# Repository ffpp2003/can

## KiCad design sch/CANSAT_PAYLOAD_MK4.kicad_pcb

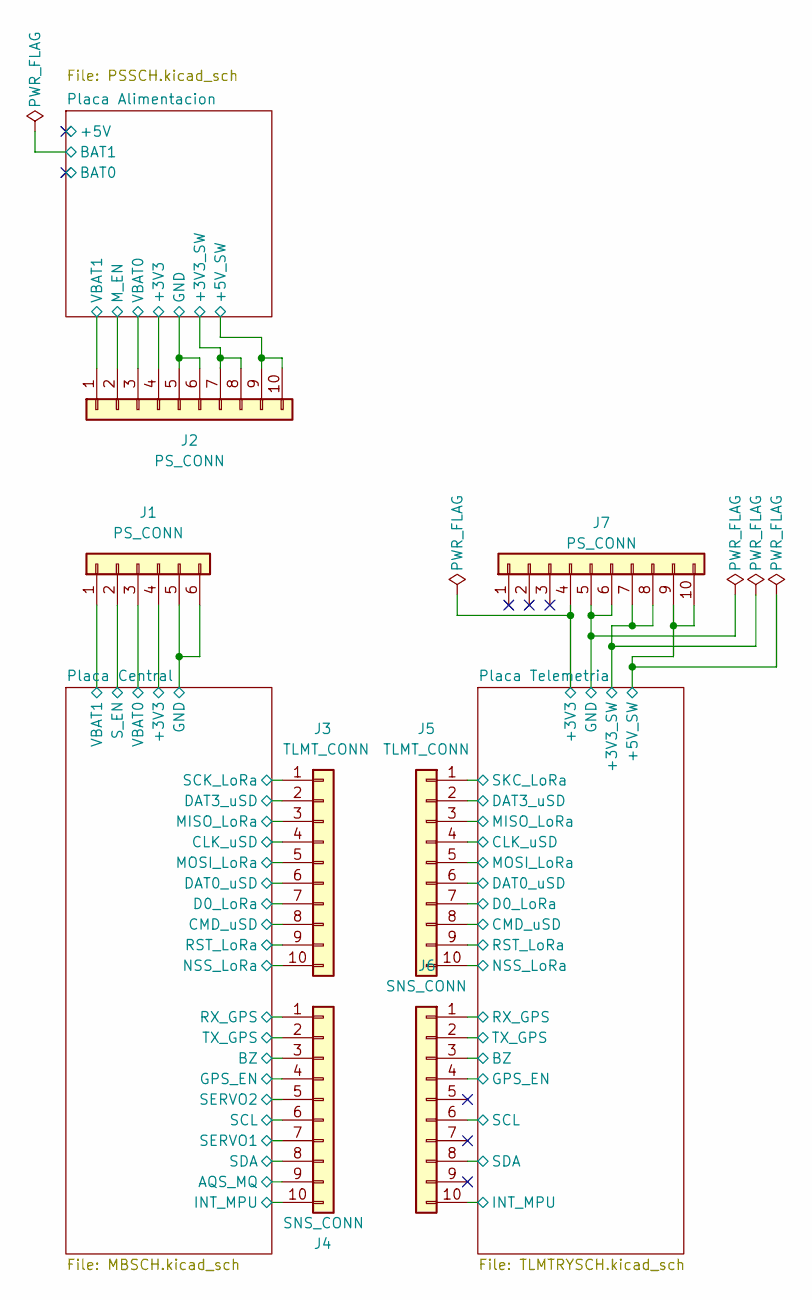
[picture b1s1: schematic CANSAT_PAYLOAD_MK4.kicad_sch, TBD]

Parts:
J1: PS_CONN; PCB_CONN_S
J2, J7: PS_CONN; PCB_CONN
J3, J5: TLMT_CONN; PCB_CONN
J4, J6: SNS_CONN; PCB_CONN

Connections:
/Placa Alimentacion/+3V3: J2.4; also elsewhere on the board
/Placa Alimentacion/+3V3_SW: J2.7, J2.8; also elsewhere on the board
/Placa Alimentacion/+5V_SW: J2.9, J2.10; also elsewhere on the board
/Placa Alimentacion/GND: J2.5, J2.6; also elsewhere on the board
/Placa Alimentacion/M_EN: J2.2; also elsewhere on the board
/Placa Alimentacion/VBAT0: J2.3; also elsewhere on the board
/Placa Alimentacion/VBAT1: J2.1; also elsewhere on the board
/Placa Central/+3V3: J1.4; also elsewhere on the board
/Placa Central/AQS_MQ: J4.9; also elsewhere on the board
/Placa Central/BZ: J4.3; also elsewhere on the board
/Placa Central/CLK_uSD: J3.4; also elsewhere on the board
/Placa Central/CMD_uSD: J3.8; also elsewhere on the board
/Placa Central/D0_LoRa: J3.7; also elsewhere on the board
/Placa Central/DAT0_uSD: J3.6; also elsewhere on the board
/Placa Central/DAT3_uSD: J3.2; also elsewhere on the board
/Placa Central/GND: J1.5, J1.6; also elsewhere on the board
/Placa Central/GPS_EN: J4.4; also elsewhere on the board
/Placa Central/INT_MPU: J4.10; also elsewhere on the board
/Placa Central/MISO_LoRa: J3.3; also elsewhere on the board
/Placa Central/MOSI_LoRa: J3.5; also elsewhere on the board
/Placa Central/NSS_LoRa: J3.10; also elsewhere on the board
/Placa Central/RST_LoRa: J3.9; also elsewhere on the board
/Placa Central/RX_GPS: J4.1; also elsewhere on the board
/Placa Central/SCK_LoRa: J3.1; also elsewhere on the board
/Placa Central/SCL: J4.6; also elsewhere on the board
/Placa Central/SDA: J4.8; also elsewhere on the board
/Placa Central/SERVO1: J4.7; also elsewhere on the board
/Placa Central/SERVO2: J4.5; also elsewhere on the board
/Placa Central/S_EN: J1.2; also elsewhere on the board
/Placa Central/TX_GPS: J4.2; also elsewhere on the board
/Placa Central/VBAT0: J1.3; also elsewhere on the board
/Placa Central/VBAT1: J1.1; also elsewhere on the board
/Placa Telemetria/+3V3: J7.4; also elsewhere on the board
/Placa Telemetria/+3V3_SW: J7.7, J7.8; also elsewhere on the board
/Placa Telemetria/+5V_SW: J7.9, J7.10; also elsewhere on the board
/Placa Telemetria/BZ: J6.3; also elsewhere on the board
/Placa Telemetria/CLK_uSD: J5.4; also elsewhere on the board
/Placa Telemetria/CMD_uSD: J5.8; also elsewhere on the board
/Placa Telemetria/D0_LoRa: J5.7; also elsewhere on the board
/Placa Telemetria/DAT0_uSD: J5.6; also elsewhere on the board
/Placa Telemetria/DAT3_uSD: J5.2; also elsewhere on the board
/Placa Telemetria/GND: J7.5, J7.6; also elsewhere on the board
/Placa Telemetria/GPS_EN: J6.4; also elsewhere on the board
/Placa Telemetria/INT_MPU: J6.10; also elsewhere on the board
/Placa Telemetria/MISO_LoRa: J5.3; also elsewhere on the board
/Placa Telemetria/MOSI_LoRa: J5.5; also elsewhere on the board
/Placa Telemetria/NSS_LoRa: J5.10; also elsewhere on the board
/Placa Telemetria/RST_LoRa: J5.9; also elsewhere on the board
/Placa Telemetria/RX_GPS: J6.1; also elsewhere on the board
/Placa Telemetria/SCL: J6.6; also elsewhere on the board
/Placa Telemetria/SDA: J6.8; also elsewhere on the board
/Placa Telemetria/SKC_LoRa: J5.1; also elsewhere on the board
/Placa Telemetria/TX_GPS: J6.2; also elsewhere on the board

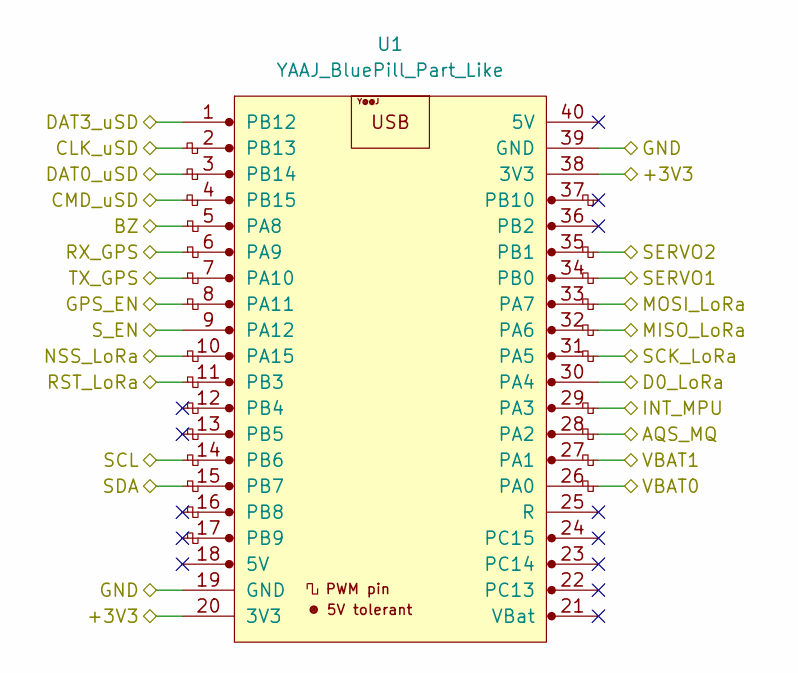
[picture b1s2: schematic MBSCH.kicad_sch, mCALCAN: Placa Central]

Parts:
U1: YAAJ_BluePill_Part_Like; YAAJ_BluePill_2

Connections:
/Placa Central/+3V3: U1.20 (3V3), U1.38 (3V3); also elsewhere on the board
/Placa Central/AQS_MQ: U1.28 (PA2); also elsewhere on the board
/Placa Central/BZ: U1.5 (PA8); also elsewhere on the board
/Placa Central/CLK_uSD: U1.2 (PB13); also elsewhere on the board
/Placa Central/CMD_uSD: U1.4 (PB15); also elsewhere on the board
/Placa Central/D0_LoRa: U1.30 (PA4); also elsewhere on the board
/Placa Central/DAT0_uSD: U1.3 (PB14); also elsewhere on the board
/Placa Central/DAT3_uSD: U1.1 (PB12); also elsewhere on the board
/Placa Central/GND: U1.19 (GND), U1.39 (GND); also elsewhere on the board
/Placa Central/GPS_EN: U1.8 (PA11); also elsewhere on the board
/Placa Central/INT_MPU: U1.29 (PA3); also elsewhere on the board
/Placa Central/MISO_LoRa: U1.32 (PA6); also elsewhere on the board
/Placa Central/MOSI_LoRa: U1.33 (PA7); also elsewhere on the board
/Placa Central/NSS_LoRa: U1.10 (PA15); also elsewhere on the board
/Placa Central/RST_LoRa: U1.11 (PB3); also elsewhere on the board
/Placa Central/RX_GPS: U1.6 (PA9); also elsewhere on the board
/Placa Central/SCK_LoRa: U1.31 (PA5); also elsewhere on the board
/Placa Central/SCL: U1.14 (PB6); also elsewhere on the board
/Placa Central/SDA: U1.15 (PB7); also elsewhere on the board
/Placa Central/SERVO1: U1.34 (PB0); also elsewhere on the board
/Placa Central/SERVO2: U1.35 (PB1); also elsewhere on the board
/Placa Central/S_EN: U1.9 (PA12); also elsewhere on the board
/Placa Central/TX_GPS: U1.7 (PA10); also elsewhere on the board
/Placa Central/VBAT0: U1.26 (PA0); also elsewhere on the board
/Placa Central/VBAT1: U1.27 (PA1); also elsewhere on the board

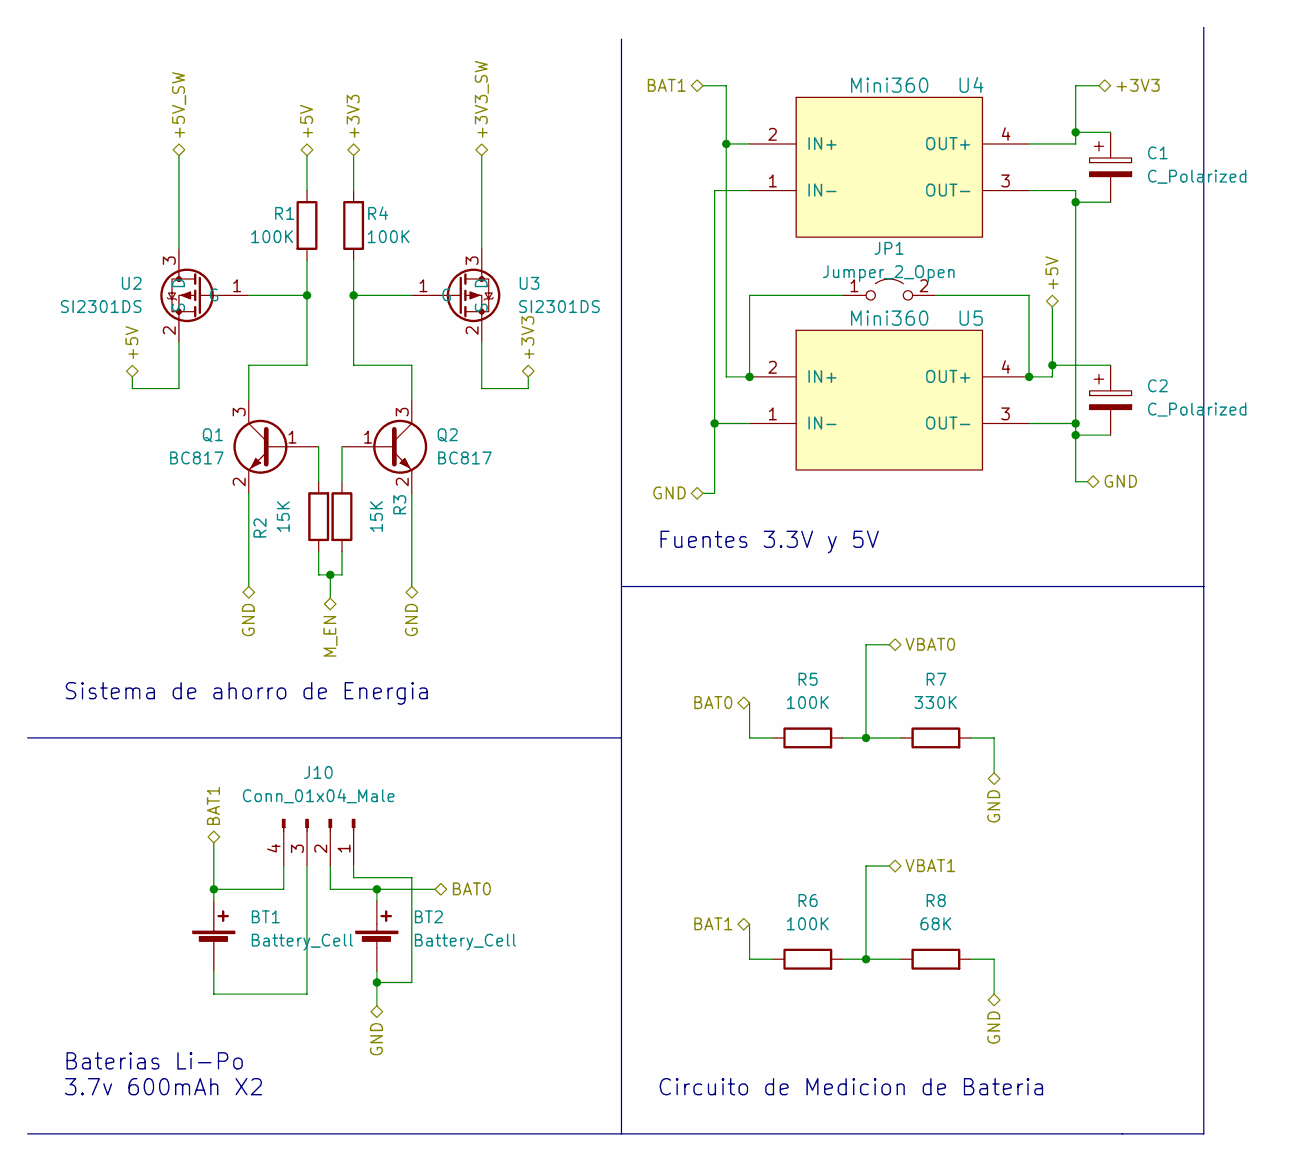
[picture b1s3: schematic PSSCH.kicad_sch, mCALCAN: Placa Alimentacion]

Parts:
BT1, BT2: Battery_Cell; Molex_Micro-Latch_53253-0270_1x02_P2.00mm_Vertical
C1, C2: C_Polarized; CP_EIA-6032-15_Kemet-U_Pad2.25x2.35mm_HandSolder
J10: Conn_01x04_Male; PinHeader_1x04_P2.54mm_Vertical
JP1: Jumper_2_Open; SolderJumper-2_P1.3mm_Open_RoundedPad1.0x1.5mm
Q1, Q2: BC817; SOT-23
R1, R4, R5, R6: 100K; R_0805_2012Metric_Pad1.20x1.40mm_HandSolder
R2, R3: 15K; R_0805_2012Metric_Pad1.20x1.40mm_HandSolder
R7: 330K; R_0805_2012Metric_Pad1.20x1.40mm_HandSolder
R8: 68K; R_0805_2012Metric_Pad1.20x1.40mm_HandSolder
U2, U3: SI2301DS; SOT-23
U4, U5: Mini360; Mini360_step-down

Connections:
/Placa Alimentacion/+3V3: C1.1, R4.2, U3.2 (S), U4.4 (OUT+); also elsewhere on the board
/Placa Alimentacion/+3V3_SW: U3.3 (D); also elsewhere on the board
/Placa Alimentacion/+5V: C2.1, JP1.2 (B), R1.1, U2.2 (S), U5.4 (OUT+)
/Placa Alimentacion/+5V_SW: U2.3 (D); also elsewhere on the board
/Placa Alimentacion/BAT0: BT2.1 (+), J10.2, R5.1
/Placa Alimentacion/BAT1: BT1.1 (+), J10.4, JP1.1 (A), R6.1, U4.2 (IN+), U5.2 (IN+)
/Placa Alimentacion/GND: BT2.2 (-), C1.2, C2.2, J10.1, Q1.2 (E), Q2.2 (E), R7.2, R8.2, U4.1 (IN-), U4.3 (OUT-), U5.1 (IN-), U5.3 (OUT-); also elsewhere on the board
/Placa Alimentacion/M_EN: R2.1, R3.2; also elsewhere on the board
/Placa Alimentacion/VBAT0: R5.2, R7.1; also elsewhere on the board
/Placa Alimentacion/VBAT1: R6.2, R8.1; also elsewhere on the board
unnamed: BT1.2 (-), J10.3
unnamed: Q1.1 (B), R2.2
unnamed: Q1.3 (C), R1.2, U2.1 (G)
unnamed: Q2.1 (B), R3.1
unnamed: Q2.3 (C), R4.1, U3.1 (G)

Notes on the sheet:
Baterias Li-Po 3.7v 600mAh X2
Sistema de ahorro de Energia
Fuentes 3.3V y 5V
Circuito de Medicion de Bateria

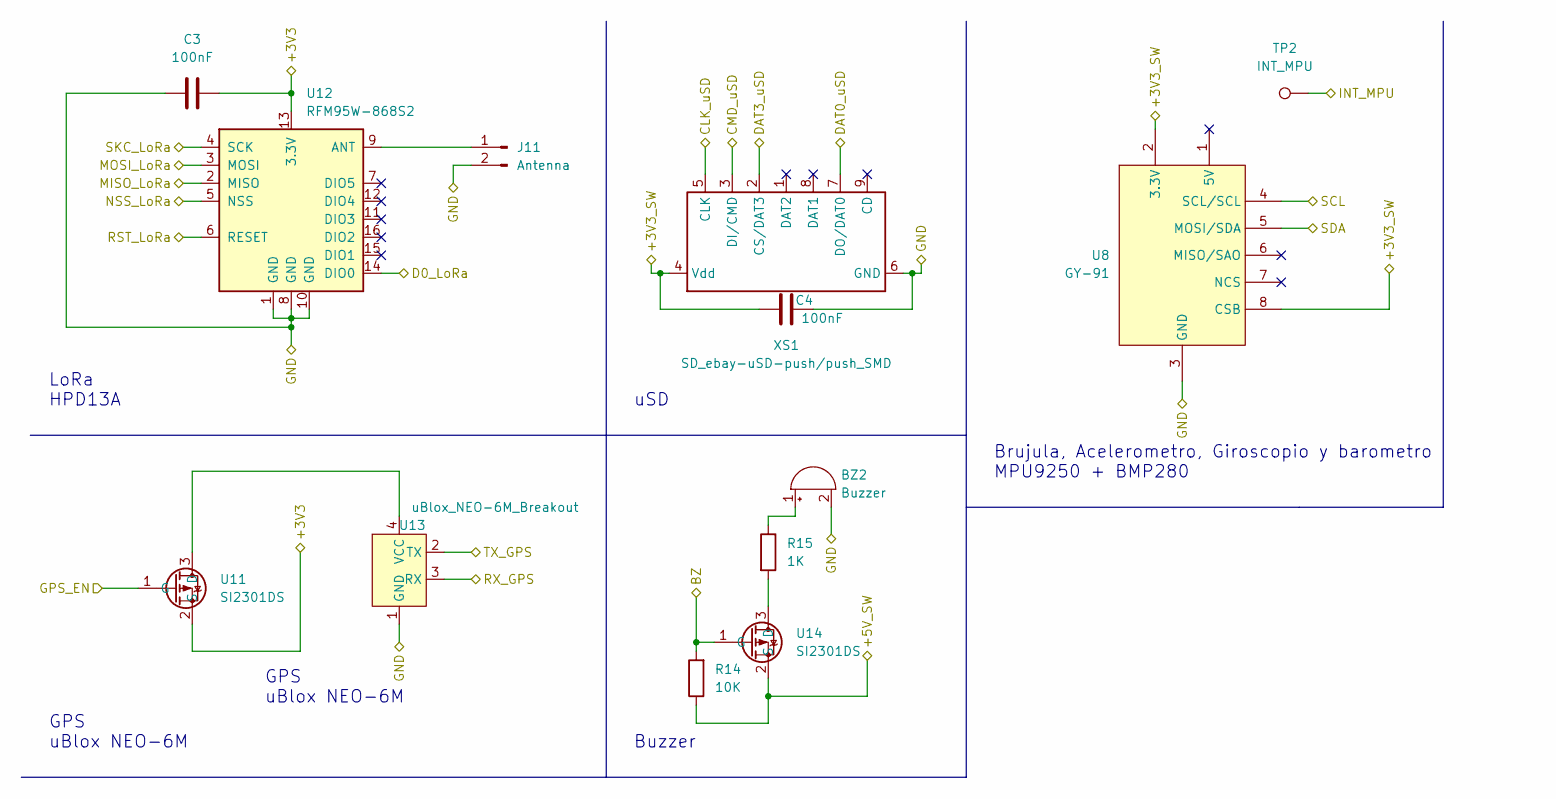
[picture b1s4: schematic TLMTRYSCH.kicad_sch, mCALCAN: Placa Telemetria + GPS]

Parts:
BZ2: Buzzer; Buzzer_12x9.5RM7.6
C3, C4: 100nF; C_0805_2012Metric_Pad1.18x1.45mm_HandSolder
J11: Antenna; U.FL_Molex_MCRF_73412-0110_Vertical
R14: 10K; R_0805_2012Metric_Pad1.20x1.40mm_HandSolder
R15: 1K; R_0805_2012Metric_Pad1.20x1.40mm_HandSolder
TP2: INT_MPU; TestPoint_THTPad_D1.5mm_Drill0.7mm
U8: GY-91; GY-91_Breakout
U11, U14: SI2301DS; SOT-23
U12: RFM95W-868S2; HOPERF_RFM9XW_SMD
U13: uBlox_NEO-6M_Breakout; uBlox-NEO-6M_Breakout
XS1: SD_ebay-uSD-push/push_SMD; Conn_uSDcard

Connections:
/Placa Telemetria/+3V3: C3.2, U11.2 (S), U12.13 (3.3V); also elsewhere on the board
/Placa Telemetria/+3V3_SW: C4.1, U8.2 (3.3V), U8.8 (CSB), XS1.4 (Vdd); also elsewhere on the board
/Placa Telemetria/+5V_SW: R14.1, U14.2 (S); also elsewhere on the board
/Placa Telemetria/BZ: R14.2, U14.1 (G); also elsewhere on the board
/Placa Telemetria/CLK_uSD: XS1.5 (CLK); also elsewhere on the board
/Placa Telemetria/CMD_uSD: XS1.3 (DI/CMD); also elsewhere on the board
/Placa Telemetria/D0_LoRa: U12.14 (DIO0); also elsewhere on the board
/Placa Telemetria/DAT0_uSD: XS1.7 (DO/DAT0); also elsewhere on the board
/Placa Telemetria/DAT3_uSD: XS1.2 (CS/DAT3); also elsewhere on the board
/Placa Telemetria/GND: BZ2.2 (+), C3.1, C4.2, J11.2, U8.3 (GND), U12.1 (GND), U12.8 (GND), U12.10 (GND), U13.1 (GND), XS1.6 (GND); also elsewhere on the board
/Placa Telemetria/GPS_EN: U11.1 (G); also elsewhere on the board
/Placa Telemetria/INT_MPU: TP2.1; also elsewhere on the board
/Placa Telemetria/MISO_LoRa: U12.2 (MISO); also elsewhere on the board
/Placa Telemetria/MOSI_LoRa: U12.3 (MOSI); also elsewhere on the board
/Placa Telemetria/NSS_LoRa: U12.5 (NSS); also elsewhere on the board
/Placa Telemetria/RST_LoRa: U12.6 (RESET); also elsewhere on the board
/Placa Telemetria/RX_GPS: U13.3 (RX); also elsewhere on the board
/Placa Telemetria/SCL: U8.4 (SCL/SCL); also elsewhere on the board
/Placa Telemetria/SDA: U8.5 (MOSI/SDA); also elsewhere on the board
/Placa Telemetria/SKC_LoRa: U12.4 (SCK); also elsewhere on the board
/Placa Telemetria/TX_GPS: U13.2 (TX); also elsewhere on the board
unnamed: BZ2.1 (-), R15.1
unnamed: J11.1, U12.9 (ANT)
unnamed: U11.3 (D), U13.4 (VCC)
unnamed: R15.2, U14.3 (D)

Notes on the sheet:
GPS uBlox NEO-6M
LoRa HPD13A
Brujula, Acelerometro, Giroscopio y barometro MPU9250 + BMP280
uSD
Buzzer

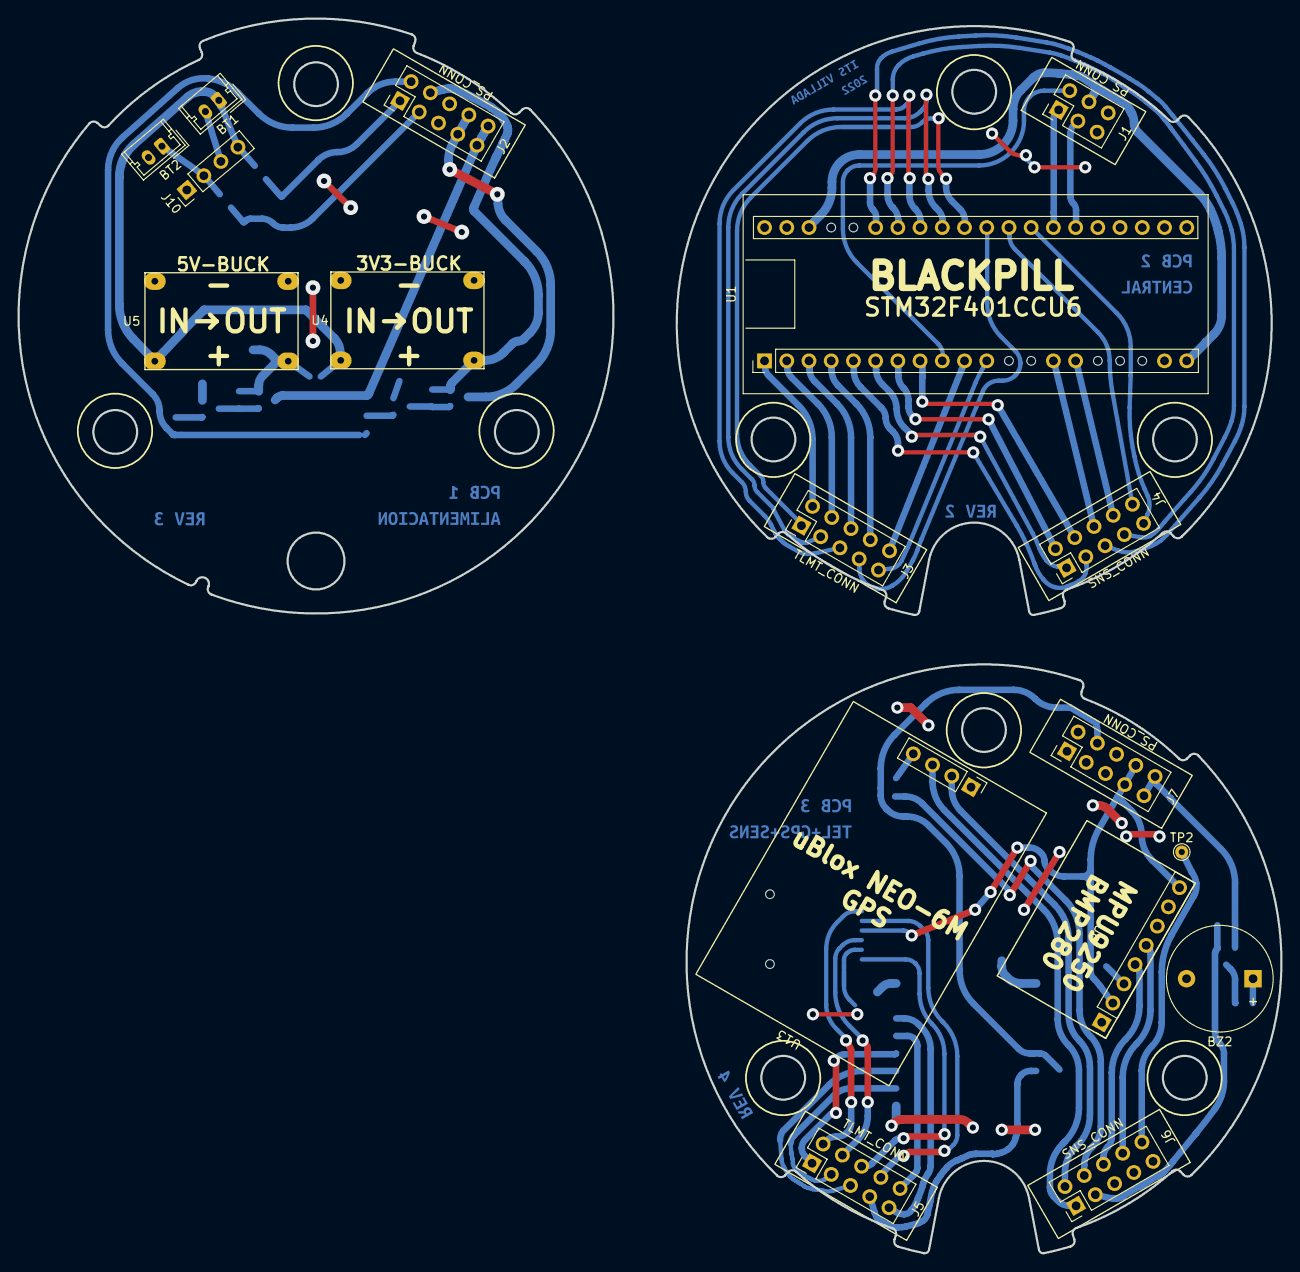
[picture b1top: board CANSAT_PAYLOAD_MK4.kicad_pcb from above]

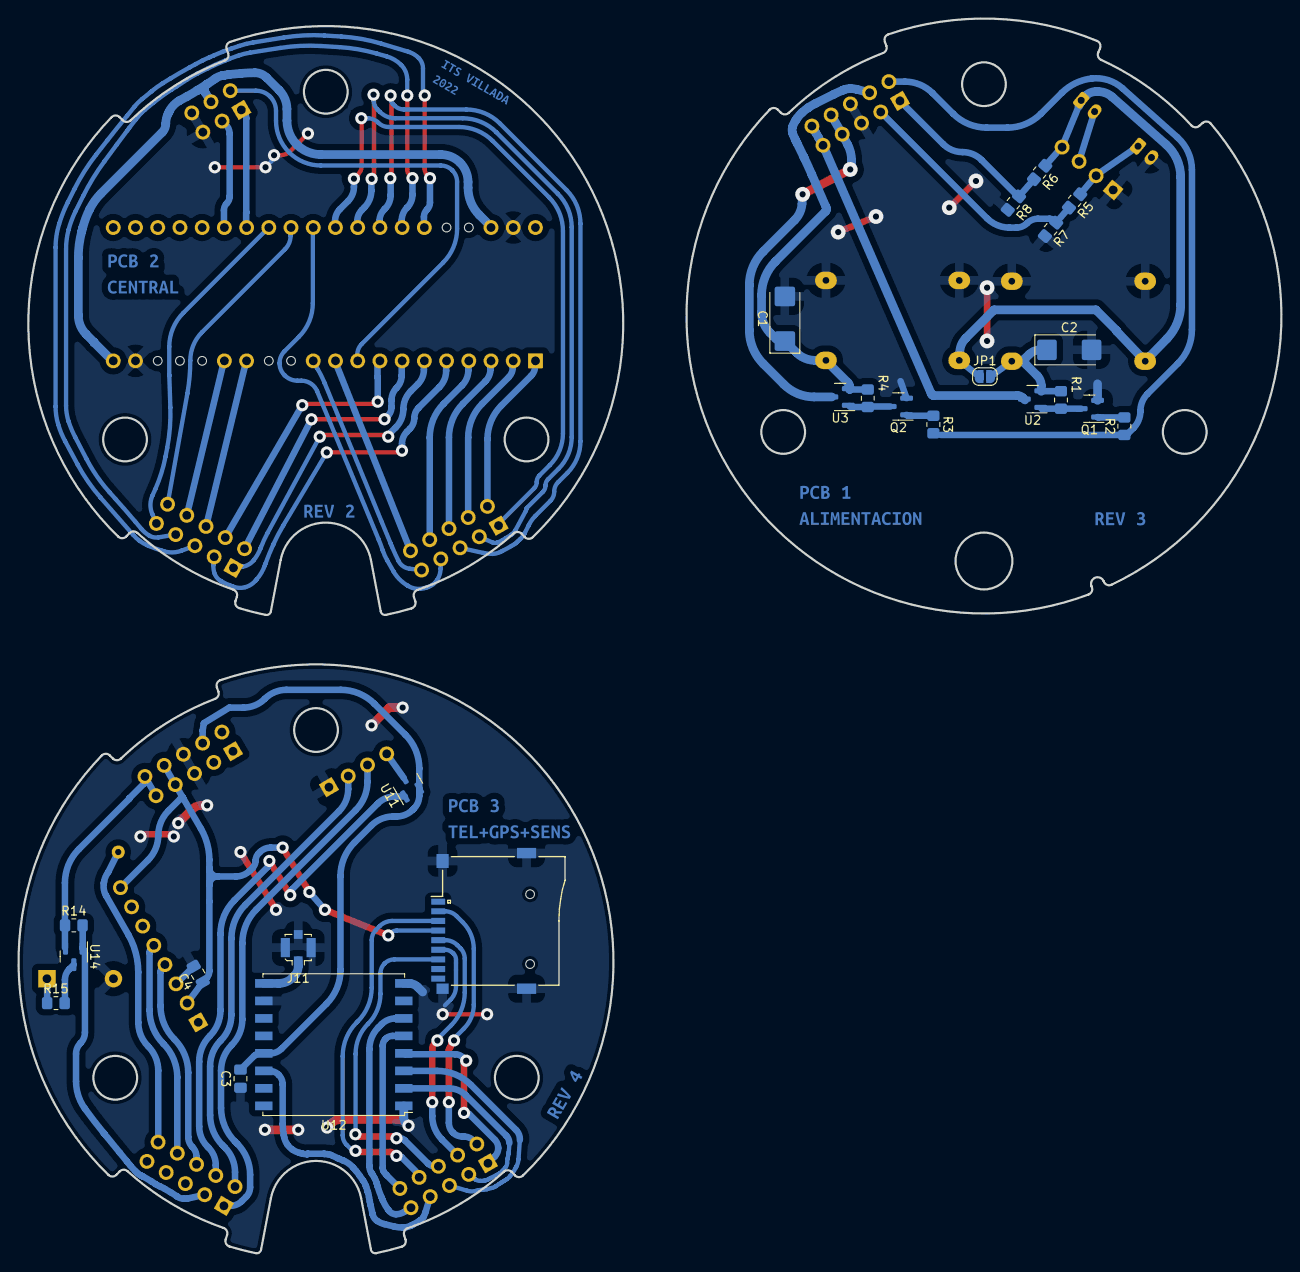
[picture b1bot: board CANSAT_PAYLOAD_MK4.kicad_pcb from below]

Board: 2 copper layers, 144.4 x 141.1 mm, 48 parts (31 on the bottom side), 65 nets.

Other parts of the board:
kibuzzard-655ED218: G***; kibuzzard-655ED218
kibuzzard-655ED392: G***; kibuzzard-655ED392
kibuzzard-655F6654: G***; kibuzzard-655F6654
kibuzzard-6319D247: G***; kibuzzard-6319D247
kibuzzard-63173E9C: G***; kibuzzard-63173E9C
kibuzzard-63173EF4: G***; kibuzzard-63173EF4
kibuzzard-634739B3: G***; kibuzzard-634739B3

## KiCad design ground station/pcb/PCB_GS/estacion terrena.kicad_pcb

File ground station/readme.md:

# Estacion Terrena

La estacion terrena del proyecto cumple la funcion de recibir los datos de la telemetria del cansat y enviarlas a la computadora a traves del puerto serial
tambien tiene la capacidad de cargar las baterias del cansat

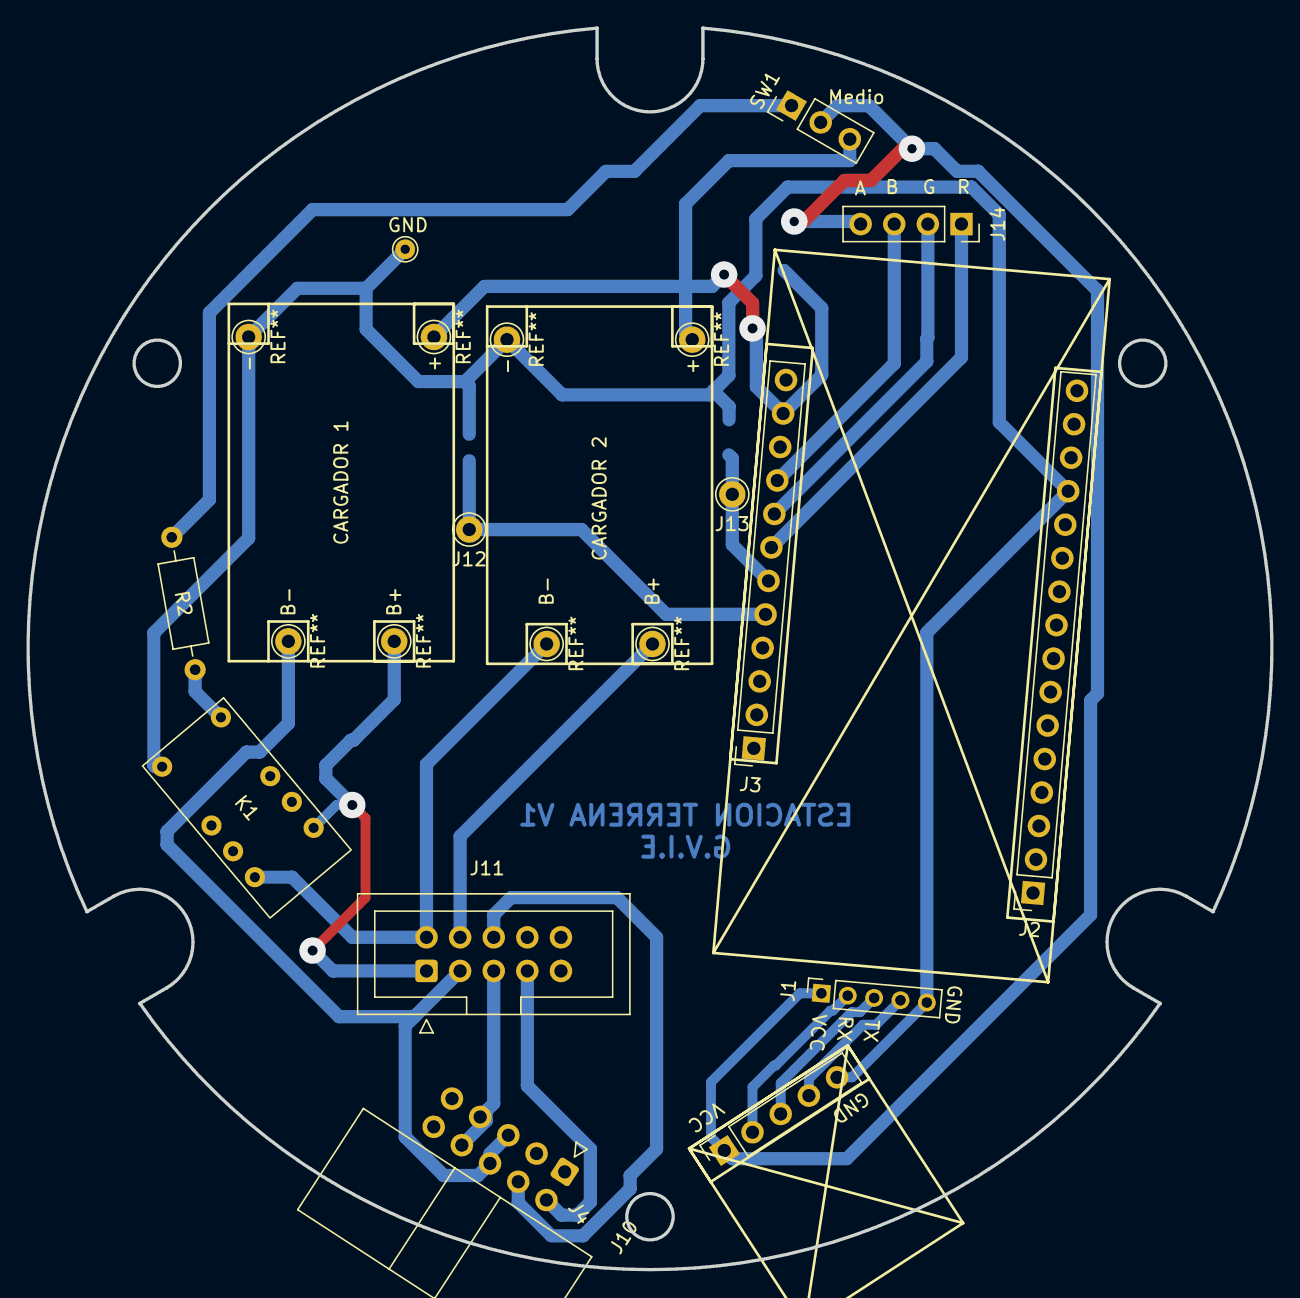
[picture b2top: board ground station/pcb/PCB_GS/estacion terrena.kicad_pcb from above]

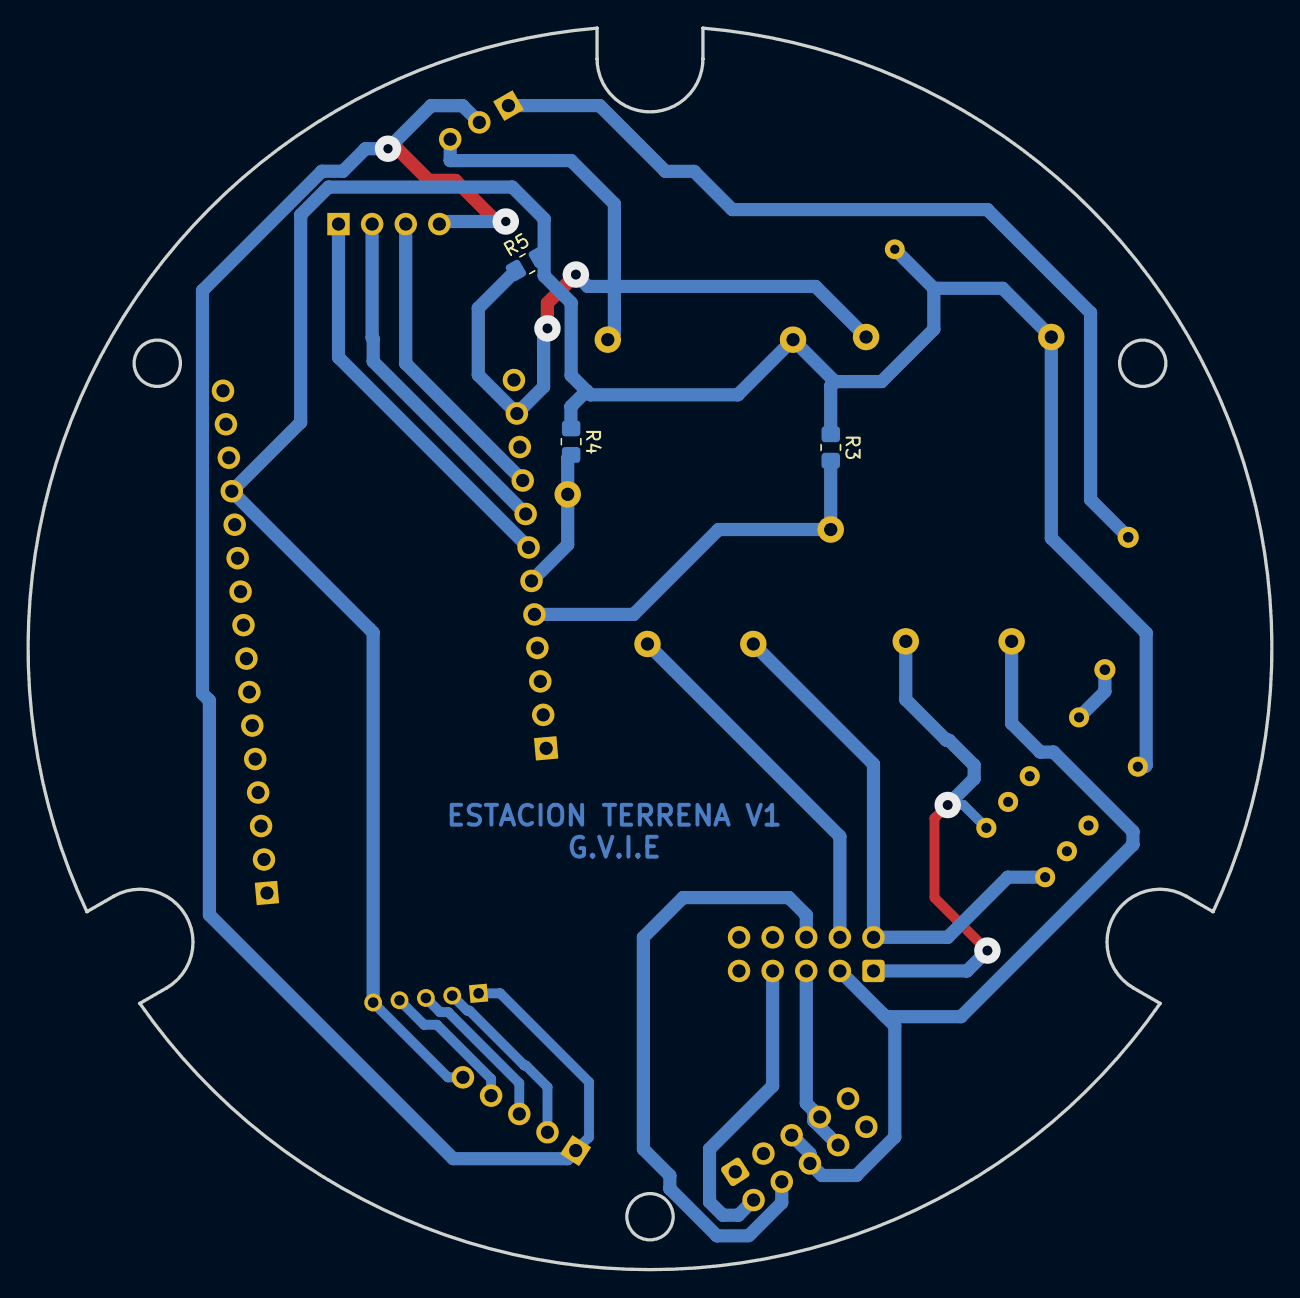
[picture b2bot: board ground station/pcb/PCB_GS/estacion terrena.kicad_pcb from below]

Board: 2 copper layers, 94.0 x 93.8 mm, 16 parts (3 on the bottom side), 19 nets.

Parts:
GND: TestPoint_THTPad_D1.5mm_Drill0.7mm
J1: Micro-usb_lora; PinSocket_1x05_P2.00mm_Vertical
J2: Parte izquierda lora; PinSocket_1x16_P2.54mm_Vertical
J3: parte derecha lora; PinSocket_1x12_P2.54mm_Vertical
J4: Breakouy_micro_usb; PinSocket_1x05_P2.54mm_Vertical
J10: IDC_STLINK; IDC-Header_2x05_P2.54mm_Horizontal
J11: IDC_CANSAT; IDC-Header_2x05_P2.54mm_Vertical
J12: LED_CARGA_1; Pin_D1.0mm_L10.0mm
J13: LED_CARGA_2; Pin_D1.0mm_L10.0mm
J14: conector RGB; PinSocket_1x04_P2.54mm_Vertical
K1: ADW11; RELAY PANASONIC
R2: 120; R_Axial_DIN0207_L6.3mm_D2.5mm_P10.16mm_Horizontal
R3, R4, R5: 10K; R_0805_2012Metric_Pad1.20x1.40mm_HandSolder
SW1: SWITCH; PinHeader_1x03_P2.54mm_Vertical

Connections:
/B: J3.9, J14.3
/G: J3.8, J14.2
/GNDBAT2: J11.2, K1.5
/LED_CARGA_1: J3.5, J12.1, R3.2
/LED_CARGA_2: J3.6, J13.1, R4.2
/NC: J1.4, J4.4
/R: J3.7, J14.1
/RX: J1.2, J4.2
/SCLK _STL_LINK: J10.2, J11.7
/SDIO_STL: J10.4, J11.6
/TX: J1.3, J4.3
/VBAT1: J11.1, K1.3
/VCC_STLINK: J10.7, J10.8, J11.5
/VCC_SW: J3.11, R5.1, SW1.3 (C)
GND: GND.1, J1.5, J2.13, J4.5, K1.6, R3.1, R4.1, R5.2
GND1: J10.5, J10.6, J11.3
unnamed: K1.1, R2.2
unnamed: R2.1, SW1.1 (A)
VCC: J1.1, J4.1, J14.4, SW1.2 (B)

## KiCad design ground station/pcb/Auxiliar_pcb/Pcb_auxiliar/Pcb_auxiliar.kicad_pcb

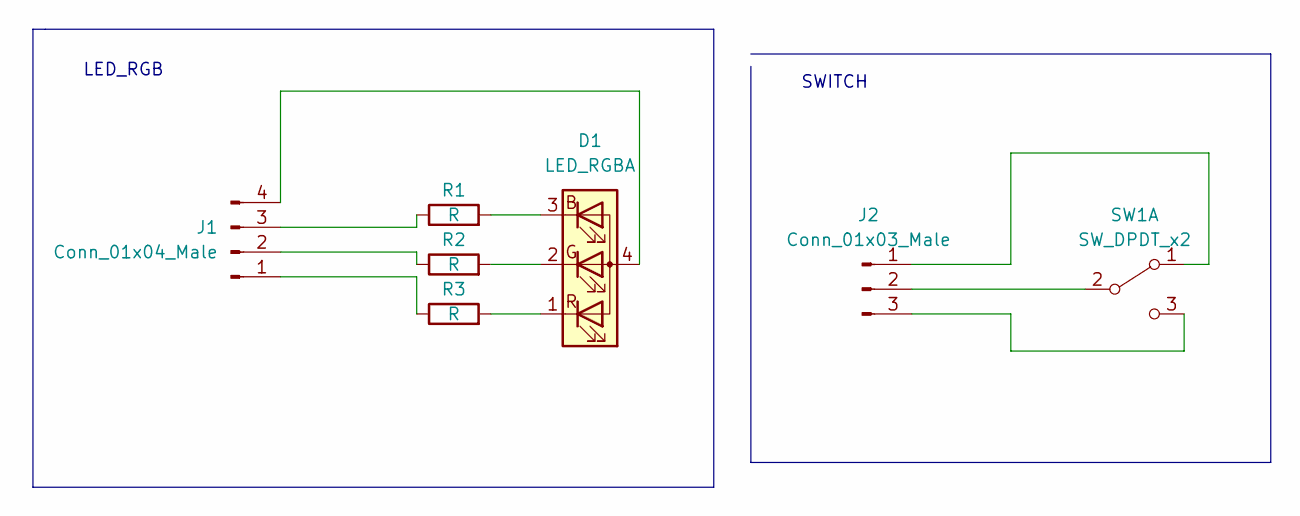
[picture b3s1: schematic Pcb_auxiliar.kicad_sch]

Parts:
D1: LED_RGBA; LED_D5.0mm-4_RGB
J1: Conn_01x04_Male; PinSocket_1x04_P2.54mm_Vertical
J2: Conn_01x03_Male; PinSocket_1x03_P2.54mm_Vertical
R1, R2, R3: R; R_0805_2012Metric
SW1: SW_DPDT_x2; SW_Slide_1P2T_CK_OS102011MS2Q

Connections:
unnamed: J1.1, R3.1
unnamed: J1.2, R2.1
unnamed: J1.3, R1.1
unnamed: D1.4 (A), J1.4
unnamed: J2.1, SW1.1 (A)
unnamed: J2.2, SW1.2 (B)
unnamed: J2.3, SW1.3 (C)
unnamed: D1.3 (BK), R1.2
unnamed: D1.2 (GK), R2.2
unnamed: D1.1 (RK), R3.2

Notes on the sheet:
SWITCH
LED_RGB

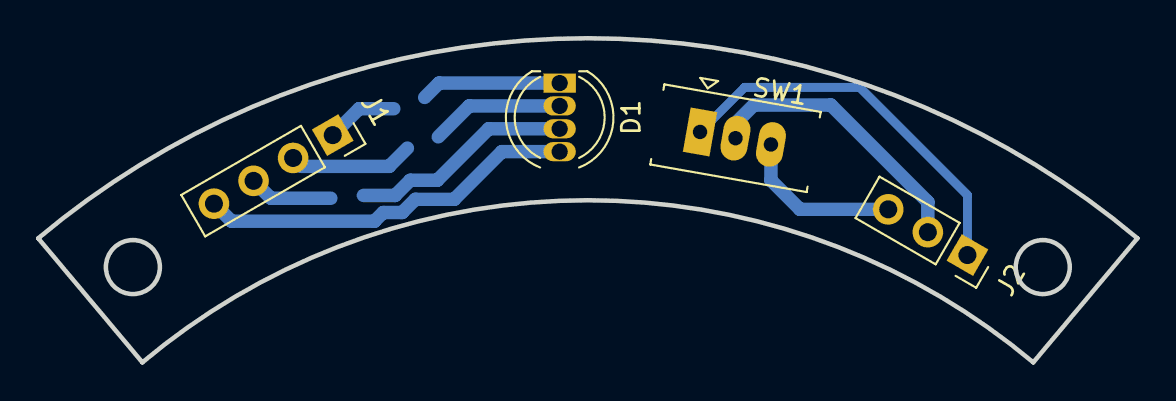
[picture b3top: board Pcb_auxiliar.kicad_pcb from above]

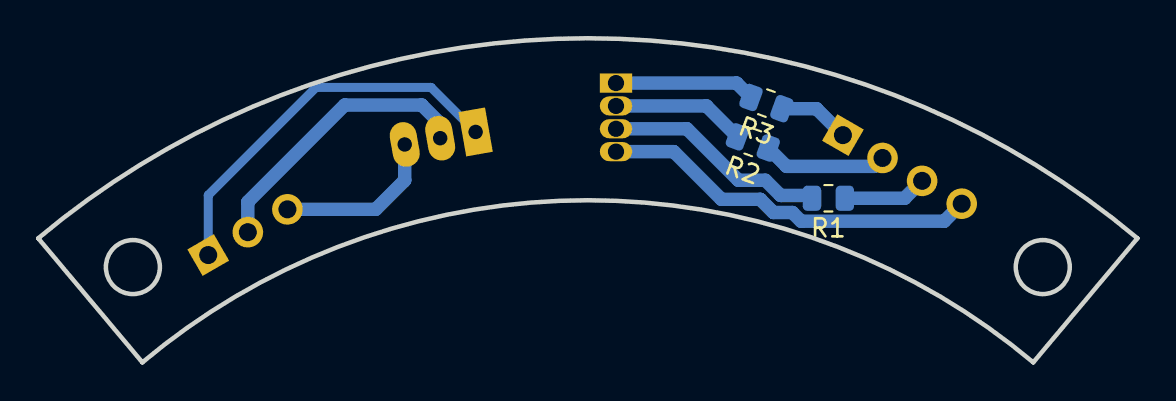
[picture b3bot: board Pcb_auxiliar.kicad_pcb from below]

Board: 2 copper layers, 61.1 x 18.0 mm, 7 parts (3 on the bottom side), 10 nets.

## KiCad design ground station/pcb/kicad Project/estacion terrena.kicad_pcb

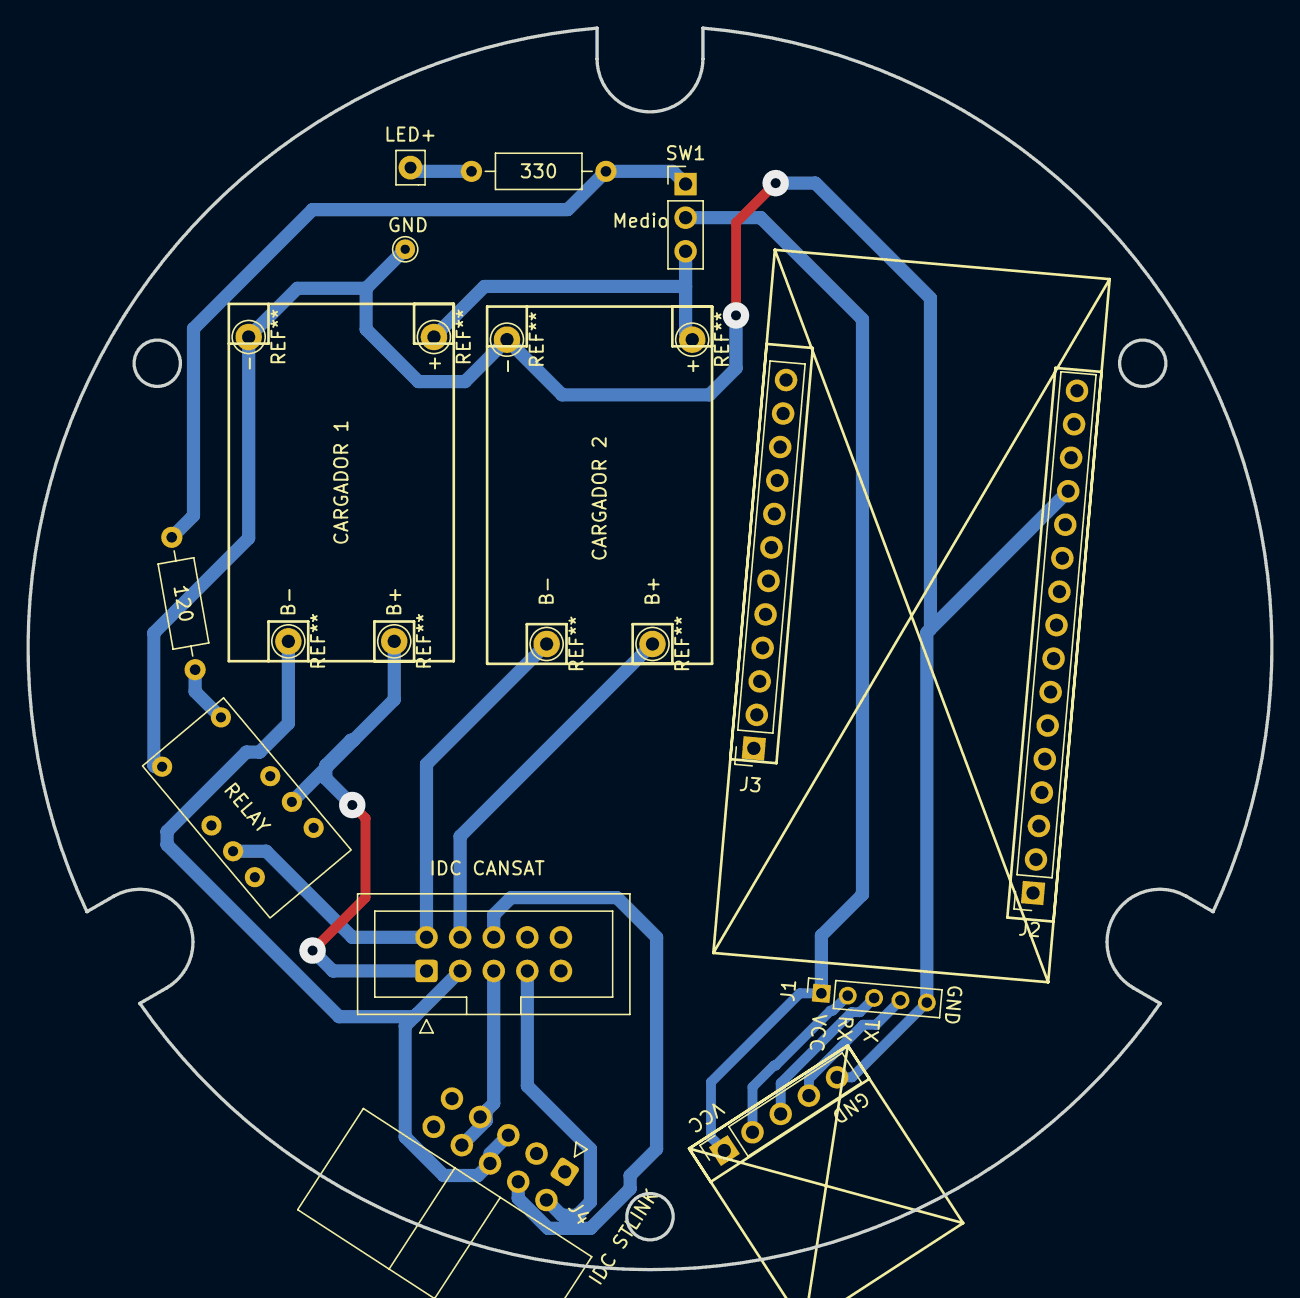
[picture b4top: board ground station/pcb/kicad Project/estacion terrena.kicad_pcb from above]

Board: 2 copper layers, 94.0 x 93.8 mm, 12 parts (0 on the bottom side), 14 nets.

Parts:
120: 120; R_Axial_DIN0207_L6.3mm_D2.5mm_P10.16mm_Horizontal
330: 330; R_Axial_DIN0207_L6.3mm_D2.5mm_P10.16mm_Horizontal
GND: TestPoint_THTPad_D1.5mm_Drill0.7mm
IDC CANSAT: IDC_CANSAT; IDC-Header_2x05_P2.54mm_Vertical
IDC STLINK: IDC_STLINK; IDC-Header_2x05_P2.54mm_Horizontal
J1: Micro-usb_lora; PinSocket_1x05_P2.00mm_Vertical
J2: Parte izquierda lora; PinSocket_1x16_P2.54mm_Vertical
J3: parte derecha lora; PinSocket_1x12_P2.54mm_Vertical
J4: Breakouy_micro_usb; PinSocket_1x05_P2.54mm_Vertical
LED+: POSITIVO_LED TESTIGO; Pin_D0.9mm_L10.0mm_W2.4mm_FlatFork
RELAY: ADW11; RELAY PANASONIC
SW1: SWITCH; PinHeader_1x03_P2.54mm_Vertical

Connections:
/GNDBAT2: IDC CANSAT.2, RELAY.5
/LED: 330.1, LED+.1
/NC: J1.4, J4.4
/RX: J1.2, J4.2
/SCLK _STL_LINK: IDC CANSAT.7, IDC STLINK.2
/SDIO_STL: IDC CANSAT.6, IDC STLINK.4
/TX: J1.3, J4.3
/VBAT1: IDC CANSAT.1, RELAY.3
/VCC_STLINK: IDC CANSAT.5, IDC STLINK.7, IDC STLINK.8
GND: GND.1, J1.5, J2.13, J4.5, RELAY.6
GND1: IDC CANSAT.3, IDC STLINK.5, IDC STLINK.6
unnamed: 120.2, RELAY.1
unnamed: 120.1, 330.2, SW1.1 (A)
VCC: J1.1, J4.1, SW1.2 (B)

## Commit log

2023-11-23 Creacion carpeta ground station
    se creo la carpeta para la estacion terrena y se movieron los archivos existentes a la carpeta
2023-11-23 creacion readme estacion terrena
2023-11-25 elimiminar viejos archivos de la ET
2023-11-25 se agregaron modelos para los bordes de las pcb
2023-11-25 created .gitignore
2023-11-27 correccion cortes
2023-11-27 added agujeros varillas corte pcb
2023-11-28 modified .gitignore
2023-11-28 added cortes para placa estacion terrena
2023-11-28 created modelo carcasa estacion terrena
2023-11-29 Se agrego Proyecto kicad Se agrego un proyecto de kicad para el diagramado y diseño de la placa
2023-11-30 removed GS pcb backups
2023-11-30 updated .gitignore
2023-11-30 Actualización
2023-11-30 AGREGADO
2023-12-01 added posicion USB
2023-12-02 Modificaciones
2023-12-02 created carpeta datasheets ET
2023-12-02 moved step pcb ET
2023-12-02 updated ET 3d models se modifico para que el idc y el usb queden colocados uno al lado del otro se agregaron modelos de antena
2023-12-02 added modelos antena ET
2023-12-02 uploaded nuevas posiciones usb e IDC
2023-12-02 ACTUALIZACION Y RERUTEO DE PLACA
2023-12-04 updated gs 3d models se agrego placa en forma de anillo se agregó agujero para el idc del stlink
2023-12-04 updated et 3d models
2023-12-04 uploaded cortes para la placa anillo de la et
2023-12-04 Adición de modificaciones y nuevo diseño de placa
2023-12-04 Actualizaciones
2023-12-06 Actualizacion
2023-12-06 created .gitignore DE NUEVO deleted backups PCB_GS
2023-12-11 Diseño actualizado - MK4
    Diseño actualizado para cumplir con la nueva misión. Se elimino una placa, el sensor de calidad de aire, servos y sensor de humedad
